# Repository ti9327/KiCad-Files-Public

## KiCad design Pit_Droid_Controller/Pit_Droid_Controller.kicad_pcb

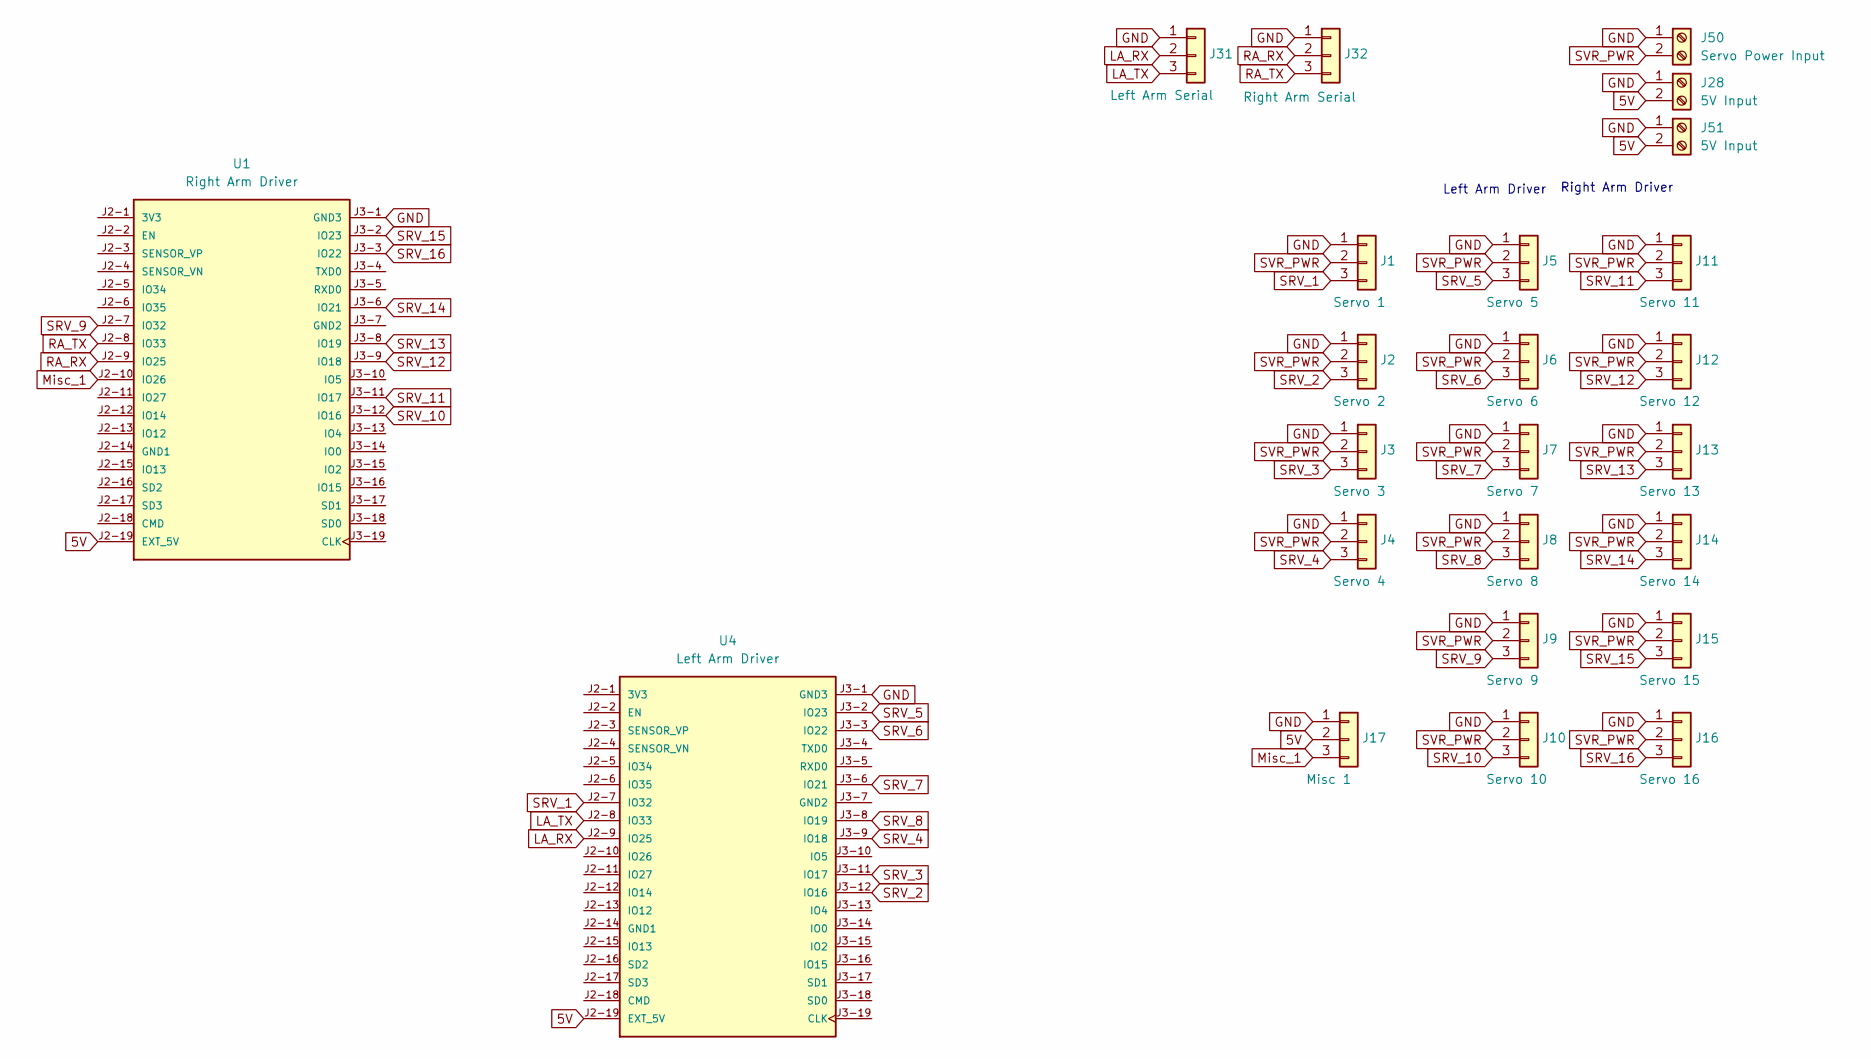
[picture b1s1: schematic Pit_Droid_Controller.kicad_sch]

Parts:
J1: Servo 1; PinHeader_1x03_P2.54mm_Vertical
J2: Servo 2; PinHeader_1x03_P2.54mm_Vertical
J3: Servo 3; PinHeader_1x03_P2.54mm_Vertical
J4: Servo 4; PinHeader_1x03_P2.54mm_Vertical
J5: Servo 5; PinHeader_1x03_P2.54mm_Vertical
J6: Servo 6; PinHeader_1x03_P2.54mm_Vertical
J7: Servo 7; PinHeader_1x03_P2.54mm_Vertical
J8: Servo 8; PinHeader_1x03_P2.54mm_Vertical
J9: Servo 9; PinHeader_1x03_P2.54mm_Vertical
J10: Servo 10; PinHeader_1x03_P2.54mm_Vertical
J11: Servo 11; PinHeader_1x03_P2.54mm_Vertical
J12: Servo 12; PinHeader_1x03_P2.54mm_Vertical
J13: Servo 13; PinHeader_1x03_P2.54mm_Vertical
J14: Servo 14; PinHeader_1x03_P2.54mm_Vertical
J15: Servo 15; PinHeader_1x03_P2.54mm_Vertical
J16: Servo 16; PinHeader_1x03_P2.54mm_Vertical
J17: Misc 1; PinHeader_1x03_P2.54mm_Vertical
J28, J51: 5V Input; TerminalBlock_Phoenix_MKDS-1,5-2-5.08_1x02_P5.08mm_Horizont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
J31: Left Arm Serial; PinHeader_1x03_P2.54mm_Vertical
J32: Right Arm Serial; PinHeader_1x03_P2.54mm_Vertical
J50: Servo Power Input; TerminalBlock_Phoenix_MKDS-1,5-2-5.08_1x02_P5.08mm_Horizont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
U1: Right Arm Driver; MODULE_ESP32-DEVKITC-32D; PARTREV V4
U4: Left Arm Driver; MODULE_ESP32-DEVKITC-32D; PARTREV V4

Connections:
5V: J17.2, J28.2, J51.2, U1.J2-19 (EXT_5V), U4.J2-19 (EXT_5V)
GND: J1.1, J2.1, J3.1, J4.1, J5.1, J6.1, J7.1, J8.1, J9.1, J10.1, J11.1, J12.1, J13.1, J14.1, J15.1, J16.1, J17.1, J28.1, J31.1, J32.1, J50.1, J51.1, U1.J3-1 (GND3), U4.J3-1 (GND3)
LA_RX: J31.2, U4.J2-9 (IO25)
LA_TX: J31.3, U4.J2-8 (IO33)
Misc_1: J17.3, U1.J2-10 (IO26)
RA_RX: J32.2, U1.J2-9 (IO25)
RA_TX: J32.3, U1.J2-8 (IO33)
SRV_1: J1.3, U4.J2-7 (IO32)
SRV_2: J2.3, U4.J3-12 (IO16)
SRV_3: J3.3, U4.J3-11 (IO17)
SRV_4: J4.3, U4.J3-9 (IO18)
SRV_5: J5.3, U4.J3-2 (IO23)
SRV_6: J6.3, U4.J3-3 (IO22)
SRV_7: J7.3, U4.J3-6 (IO21)
SRV_8: J8.3, U4.J3-8 (IO19)
SRV_9: J9.3, U1.J2-7 (IO32)
SRV_10: J10.3, U1.J3-12 (IO16)
SRV_11: J11.3, U1.J3-11 (IO17)
SRV_12: J12.3, U1.J3-9 (IO18)
SRV_13: J13.3, U1.J3-8 (IO19)
SRV_14: J14.3, U1.J3-6 (IO21)
SRV_15: J15.3, U1.J3-2 (IO23)
SRV_16: J16.3, U1.J3-3 (IO22)
SVR_PWR: J1.2, J2.2, J3.2, J4.2, J5.2, J6.2, J7.2, J8.2, J9.2, J10.2, J11.2, J12.2, J13.2, J14.2, J15.2, J16.2, J50.2

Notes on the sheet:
Left Arm Driver
Right Arm Driver

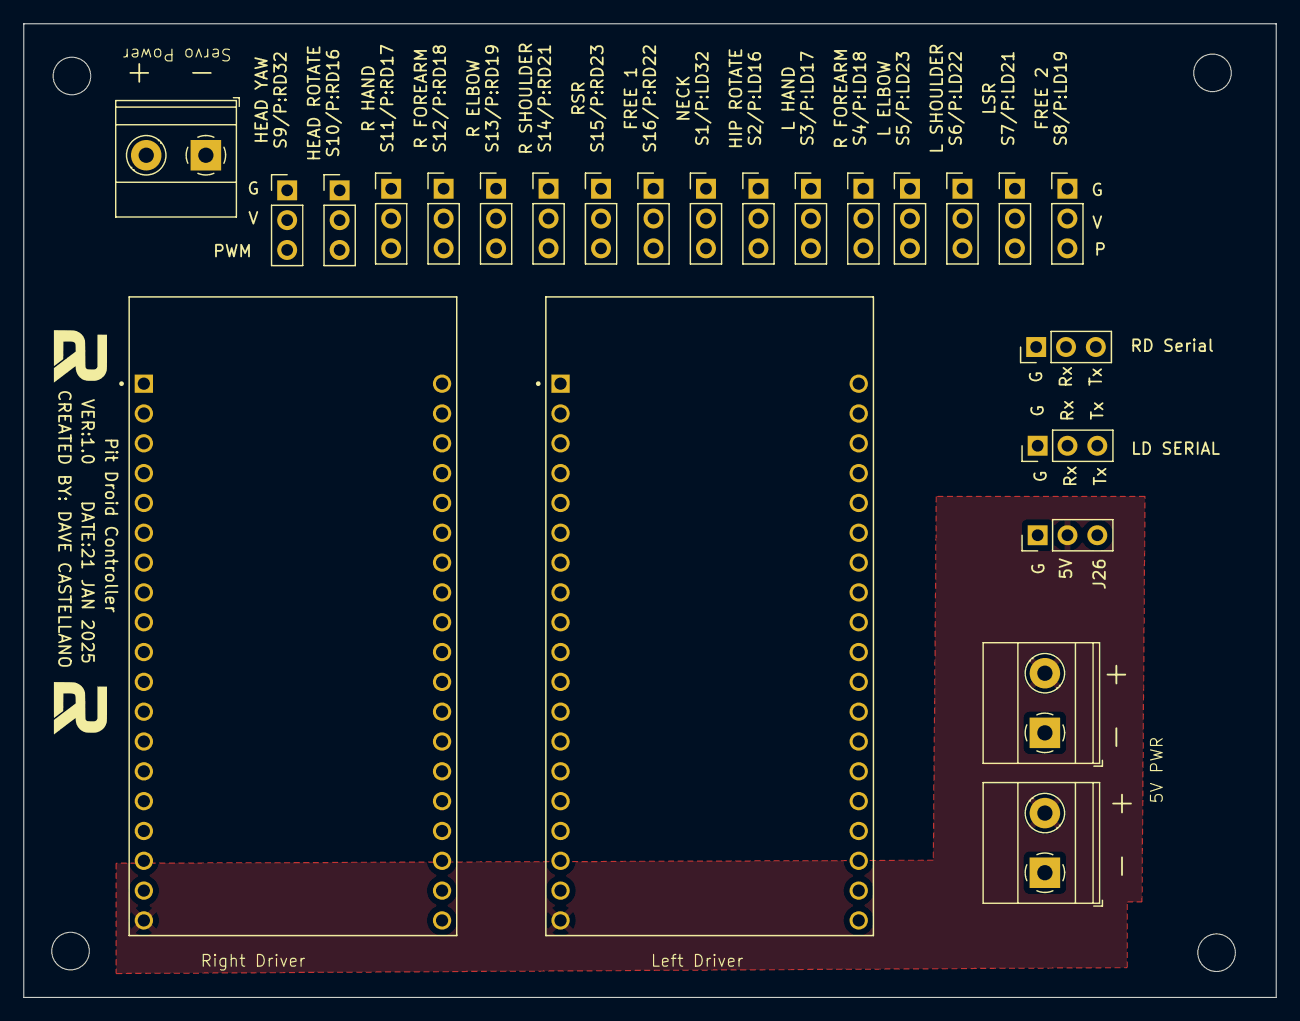
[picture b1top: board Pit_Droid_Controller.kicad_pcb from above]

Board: 4 copper layers, 106.7 x 82.9 mm, 24 parts (0 on the bottom side), 24 nets.

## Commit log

2025-01-27 New Dual ESP32 Controller
